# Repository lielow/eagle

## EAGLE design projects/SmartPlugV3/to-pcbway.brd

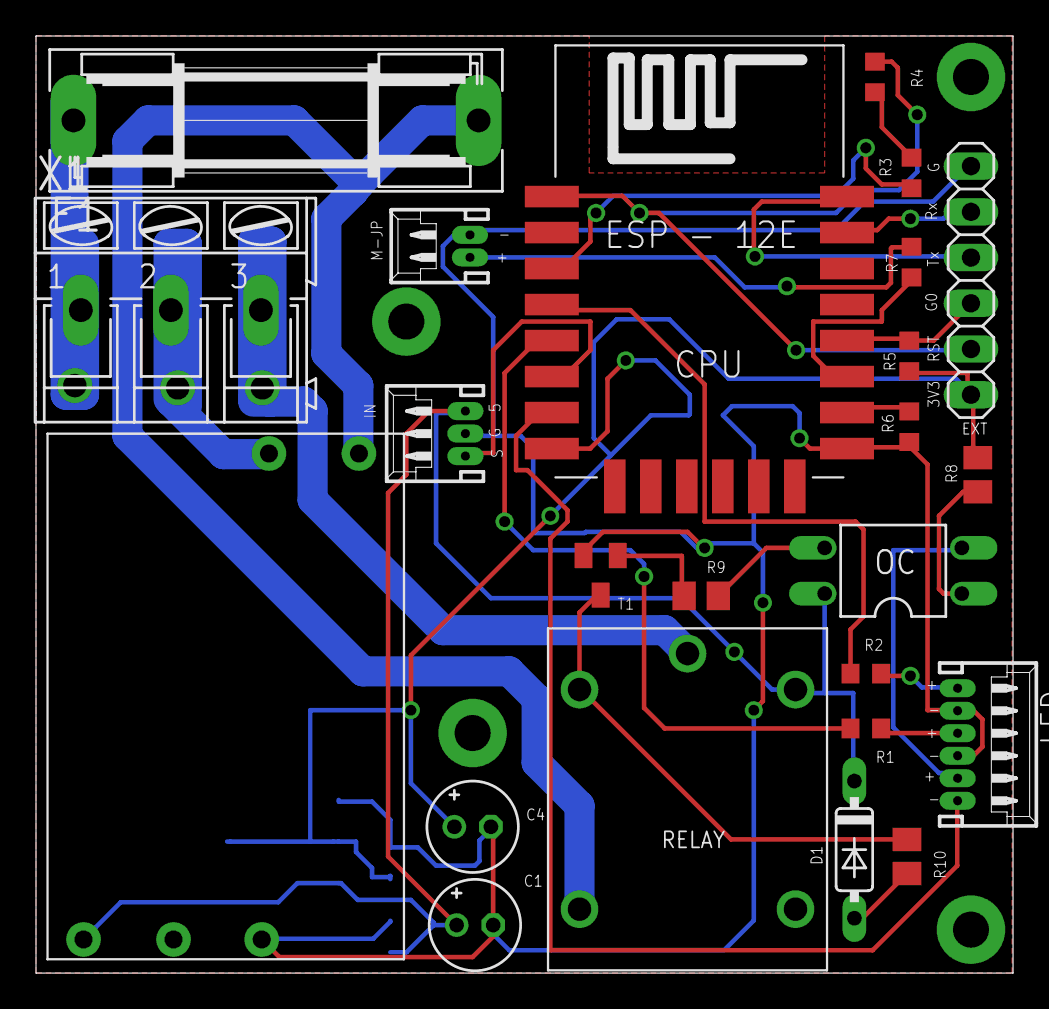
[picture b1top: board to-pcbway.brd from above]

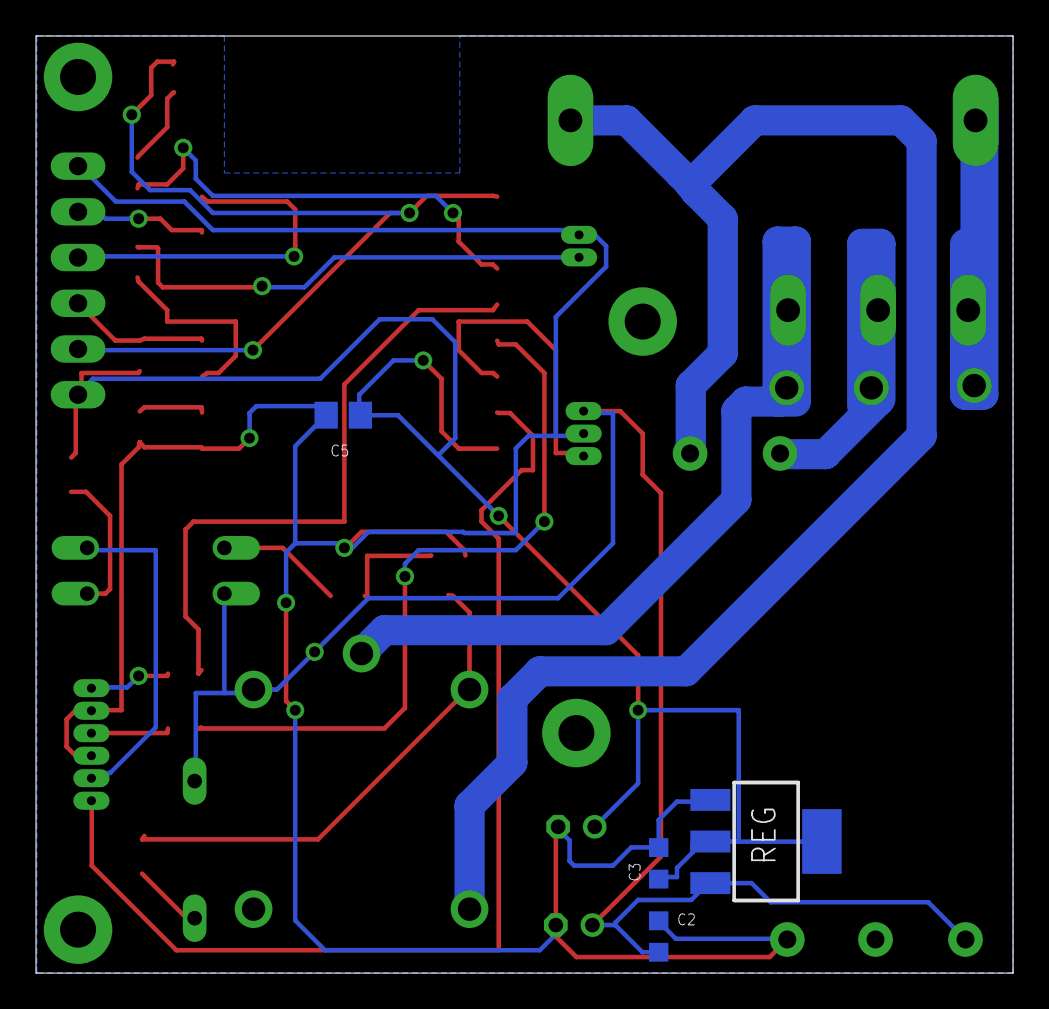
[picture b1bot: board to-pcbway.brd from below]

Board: 2 copper layers, 54.3 x 52.1 mm, 28 parts (4 on the bottom side), 27 nets.

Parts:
C1, C4: E2-5
C2, C3: C0603K
C5: C0805
CPU: ESP12E-SMD
D1: DO35-7
EXT: 1X06
F1: SH22,5
IN: 53048-03
LED: 53048-06
M-JP: 53048-02
OC: DIL04
R1, R2, R3, R4, R5, R6, R7: R0603
R8, R9, R10: M0805
REG: SOT-223
RELAY: RELAY-SONGLE
T1: SOT23-BEC
U$4: POWERSUPPLY-5V-700MA
X1: AK300/3

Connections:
3V3: C3.1, C4.+, C5.1, CPU.VCC, EXT.1, R3.2, R4.2, R5.2, R8.1, REG.2, REG.4
+5V: C1.+, C2.1, D1.C, IN.1, OC.4, REG.3, RELAY.V+, U$4.5V
COM: RELAY.COM, X1.3
EN: CPU.CH_PD, R3.1
G-00: CPU.GPIO0, EXT.3, R5.1
G-12: CPU.GPIO12, IN.3
G-13: CPU.GPIO13, LED.1
G-15: CPU.GPIO15, R6.2
GND: C1.-, C2.2, C3.2, C4.-, C5.2, CPU.GND, EXT.6, IN.2, LED.3, LED.5, M-JP.1, R6.1, REG.1, T1.E, U$4.GND
LED-ESP+: LED.6, R2.1
LED-RELAY+: LED.2, OC.2
LED-STATUS+: LED.4, R1.1
LINE: F1.1, X1.1
M-SW+: M-JP.2, R7.1
N: U$4.AC2, X1.2
unnamed: OC.3, R9.1
unnamed: R9.2, T1.B
unnamed: CPU.GPIO16, R2.2
unnamed: CPU.GPIO2, R7.2
unnamed: CPU.GPIO14, R1.2
unnamed: OC.1, R8.2
unnamed: D1.A, R10.2
unnamed: R10.1, RELAY.V-, T1.C
RELAY-NO: F1.2, RELAY.NO, U$4.AC1
RST: CPU.RESET, EXT.2, R4.1
RX: CPU.RXD0, EXT.5
TX: CPU.TXD0, EXT.4

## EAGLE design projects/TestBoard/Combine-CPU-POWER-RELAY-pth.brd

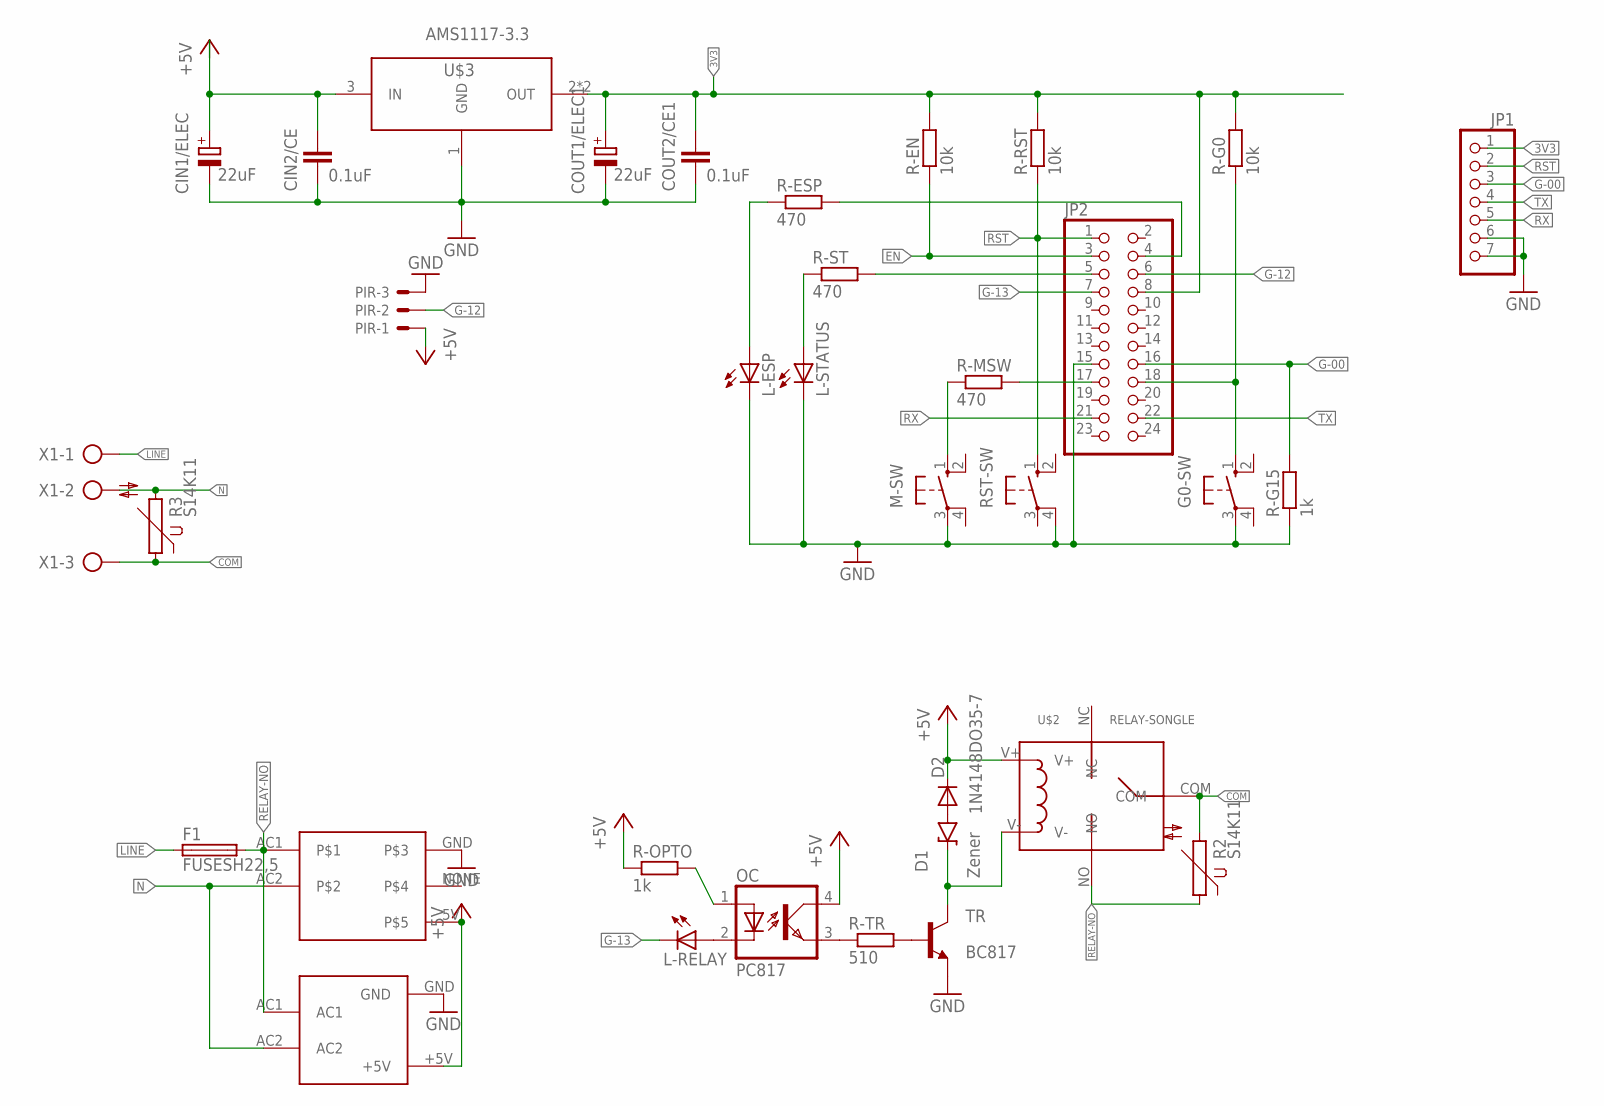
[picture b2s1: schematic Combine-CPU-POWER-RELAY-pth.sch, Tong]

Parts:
CIN1/ELEC: 22uF; E2,5-5
CIN2/CE: 0.1uF; C050-024X044
COUT1/ELEC1: 22uF; E2,5-5
COUT2/CE1: 0.1uF; C050-024X044
D1: Zener; DIODE-ZENER
D2: 1N4148DO35-7; DO35-7
F1: FUSESH22,5; SH22,5
G0-SW: 10-XX; B3F-10XX
JP1: PINHD-1X7; 1X07
JP2: PINHD-2X12; 2X12
L-ESP: LED3MM
L-RELAY: LED3MM
L-STATUS: LED3MM
M-SW: 10-XX; B3F-10XX
OC: PC817; DIL04
PIR: 53048-03
R2, R3: S14K11
R-EN: 10k; 0207/2V
R-ESP: 470; 0207/2V
R-G0: 10k; 0207/2V
R-G15: 1k; 0207/2V
R-MSW: 470; 0207/2V
R-OPTO: 1k; 0207/2V
R-RST: 10k; 0207/2V
R-ST: 470; 0207/2V
R-TR: 510; 0207/2V
RST-SW: 10-XX; B3F-10XX
TR: BC817; SOT23-BEC
U$1: HLK-PM01
U$2: RELAY-SONGLE
U$3: AMS1117-3.3; SOT-223
U$4: POWERSUPPLY-5V-700MA
X1: AK300/3

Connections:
3V3: COUT1/ELEC1.+, COUT2/CE1.1, JP1.1, JP2.8, R-EN.2, R-G0.2, R-RST.2, U$3.2 (OUT), U$3.4 (OUT)
+5V: CIN1/ELEC.+, CIN2/CE.1, D2.C, OC.4 (COL), PIR.1, R-OPTO.1, U$1.+5V, U$2.V+, U$3.3 (IN), U$4.5V
COM: R2.2, R3.1, U$2.COM, X1.3
EN: JP2.3, R-EN.1
G-00: JP1.3, JP2.16, R-G15.2
G-12: JP2.6, PIR.2
G-13: JP2.7, L-RELAY.K (C)
GND: CIN1/ELEC.-, CIN2/CE.2, COUT1/ELEC1.-, COUT2/CE1.2, G0-SW.3, JP1.6, JP1.7, JP2.15, L-ESP.K (C), L-STATUS.K (C), M-SW.3, PIR.3, R-G15.1, RST-SW.4 (P1), TR.E, U$1.GND, U$3.1 (GND), U$4.GND
LINE: F1.1, X1.1
N: R3.2, U$1.AC2, U$4.AC2, X1.2
unnamed: OC.3 (EMIT), R-TR.1
unnamed: R-TR.2, TR.B
unnamed: D1.P$2 (A), D2.A
unnamed: JP2.17, R-MSW.2
unnamed: JP2.5, R-ST.2
unnamed: OC.1 (A), R-OPTO.2
unnamed: D1.P$1 (C), TR.C, U$2.V-
unnamed: JP2.4, R-ESP.2
unnamed: L-RELAY.A, OC.2 (C)
unnamed: M-SW.1 (S), R-MSW.1
unnamed: L-STATUS.A, R-ST.1
unnamed: L-ESP.A, R-ESP.1
unnamed: G0-SW.1 (S), JP2.18, R-G0.1
RELAY-NO: F1.2, R2.1, U$1.AC1, U$2.NO, U$4.AC1
RST: JP1.2, JP2.1, R-RST.1, RST-SW.1 (S)
RX: JP1.5, JP2.21
TX: JP1.4, JP2.22

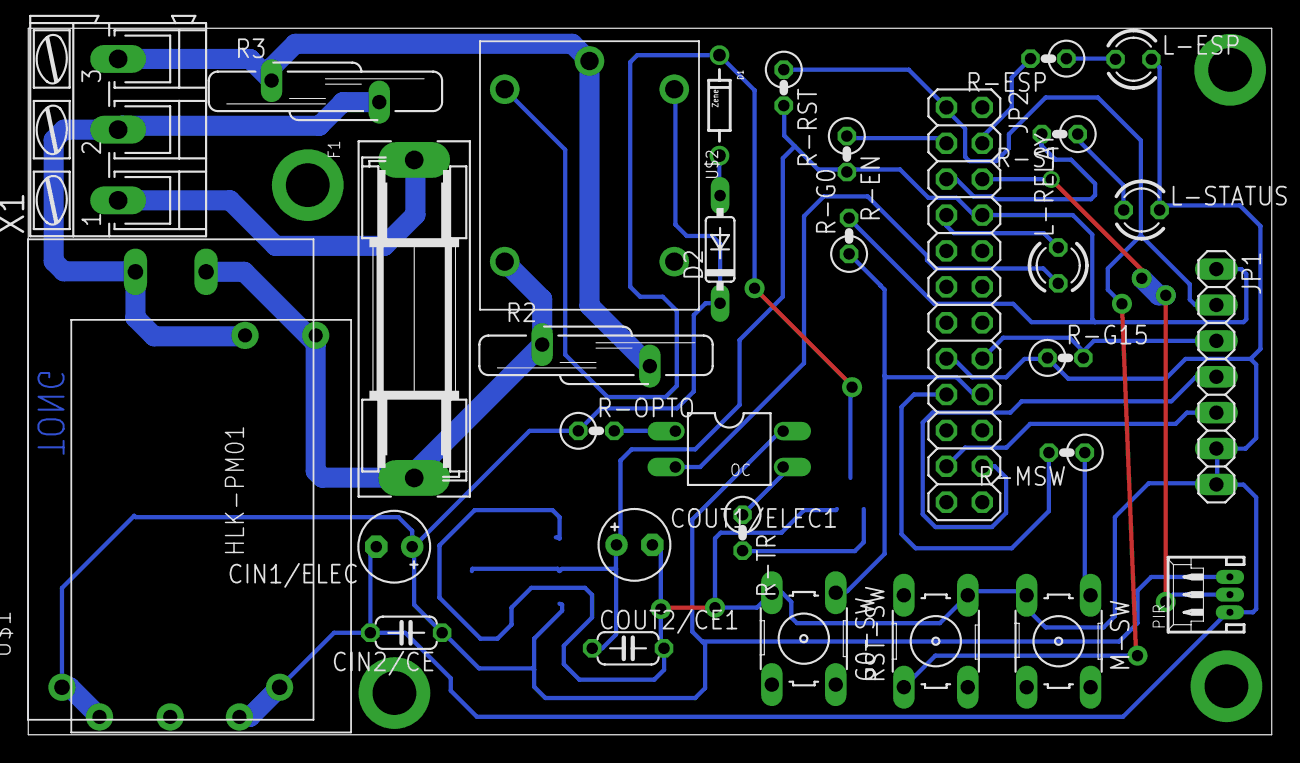
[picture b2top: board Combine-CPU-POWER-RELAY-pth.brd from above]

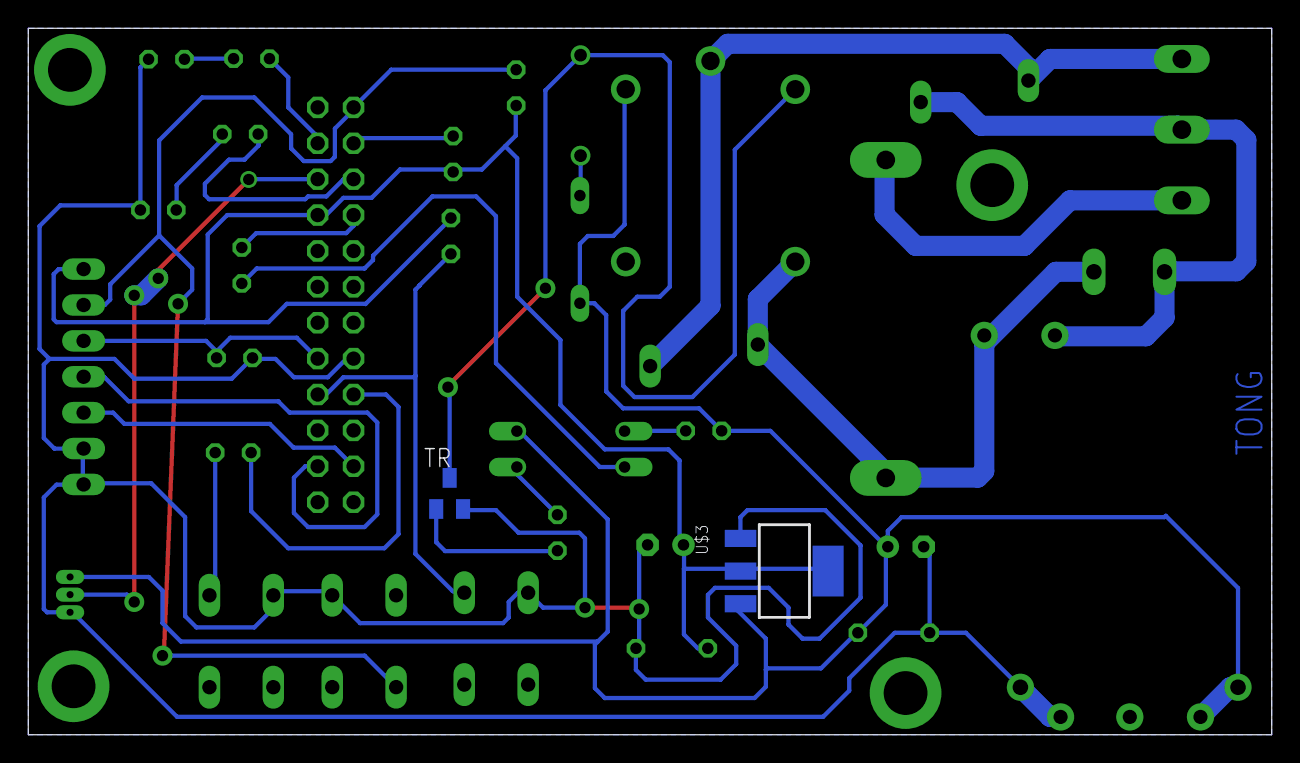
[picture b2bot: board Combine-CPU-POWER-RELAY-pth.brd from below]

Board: 2 copper layers, 88.0 x 50.0 mm, 34 parts (2 on the bottom side), 27 nets.

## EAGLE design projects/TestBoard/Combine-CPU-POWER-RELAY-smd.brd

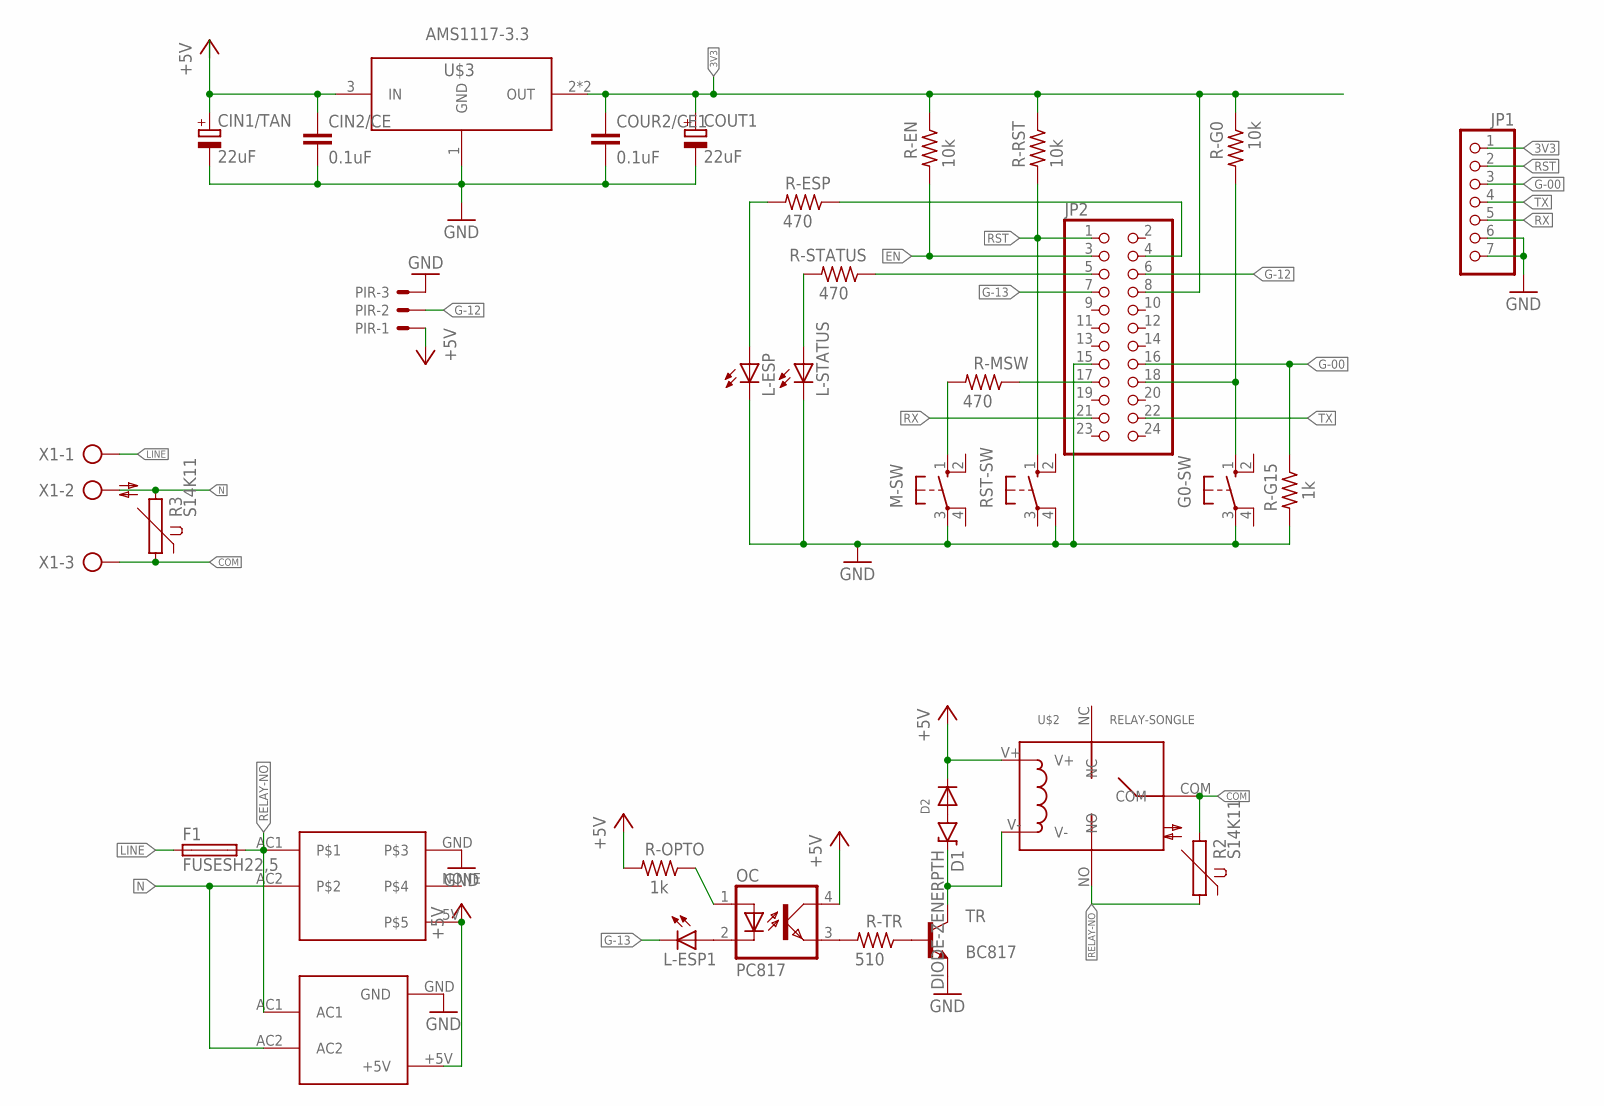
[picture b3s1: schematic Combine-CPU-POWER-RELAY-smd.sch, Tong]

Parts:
CIN1/TAN: 22uF; B/3528-21R
CIN2/CE: 0.1uF; C0805
COUR2/CE1: 0.1uF; C0805
COUT1: 22uF; B/3528-21R
D1: DIODE-ZENERPTH; DIODE-ZENER
D2: DIODESMA; SMADIODE
F1: FUSESH22,5; SH22,5
G0-SW: 10-XX; B3F-10XX
JP1: PINHD-1X7; 1X07
JP2: PINHD-2X12; 2X12
L-ESP, L-ESP1: LED3MM
L-STATUS: LED3MM
M-SW: 10-XX; B3F-10XX
OC: PC817; DIL04
PIR: 53048-03
R2, R3: S14K11
R-EN: 10k; M0805
R-ESP: 470; M0805
R-G0: 10k; M0805
R-G15: 1k; M0805
R-MSW: 470; M0805
R-OPTO: 1k; M0805
R-RST: 10k; M0805
R-STATUS: 470; M0805
R-TR: 510; M0805
RST-SW: 10-XX; B3F-10XX
TR: BC817; SOT23-BEC
U$1: HLK-PM01
U$2: RELAY-SONGLE
U$3: AMS1117-3.3; SOT-223
U$4: POWERSUPPLY-5V-700MA
X1: AK300/3

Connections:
3V3: COUR2/CE1.1, COUT1.+, JP1.1, JP2.8, R-EN.1, R-G0.1, R-RST.1, U$3.2 (OUT), U$3.4 (OUT)
+5V: CIN1/TAN.+, CIN2/CE.1, D2.C, OC.4 (COL), PIR.1, R-OPTO.2, U$1.+5V, U$2.V+, U$3.3 (IN), U$4.5V
COM: R2.2, R3.1, U$2.COM, X1.3
EN: JP2.3, R-EN.2
G-00: JP1.3, JP2.16, R-G15.1
G-12: JP2.6, PIR.2
G-13: JP2.7, L-ESP1.K (C)
GND: CIN1/TAN.-, CIN2/CE.2, COUR2/CE1.2, COUT1.-, G0-SW.3, JP1.6, JP1.7, JP2.15, L-ESP.K (C), L-STATUS.K (C), M-SW.3, PIR.3, R-G15.2, RST-SW.4 (P1), TR.E, U$1.GND, U$3.1 (GND), U$4.GND
LINE: F1.1, X1.1
N: R3.2, U$1.AC2, U$4.AC2, X1.2
unnamed: OC.3 (EMIT), R-TR.2
unnamed: R-TR.1, TR.B
unnamed: JP2.17, R-MSW.1
unnamed: JP2.5, R-STATUS.1
unnamed: OC.1 (A), R-OPTO.1
unnamed: D1.P$2 (A), D2.A
unnamed: D1.P$1 (C), TR.C, U$2.V-
unnamed: JP2.4, R-ESP.1
unnamed: L-ESP1.A, OC.2 (C)
unnamed: M-SW.1 (S), R-MSW.2
unnamed: L-STATUS.A, R-STATUS.2
unnamed: L-ESP.A, R-ESP.2
unnamed: G0-SW.1 (S), JP2.18, R-G0.2
RELAY-NO: F1.2, R2.1, U$1.AC1, U$2.NO, U$4.AC1
RST: JP1.2, JP2.1, R-RST.2, RST-SW.1 (S)
RX: JP1.5, JP2.21
TX: JP1.4, JP2.22

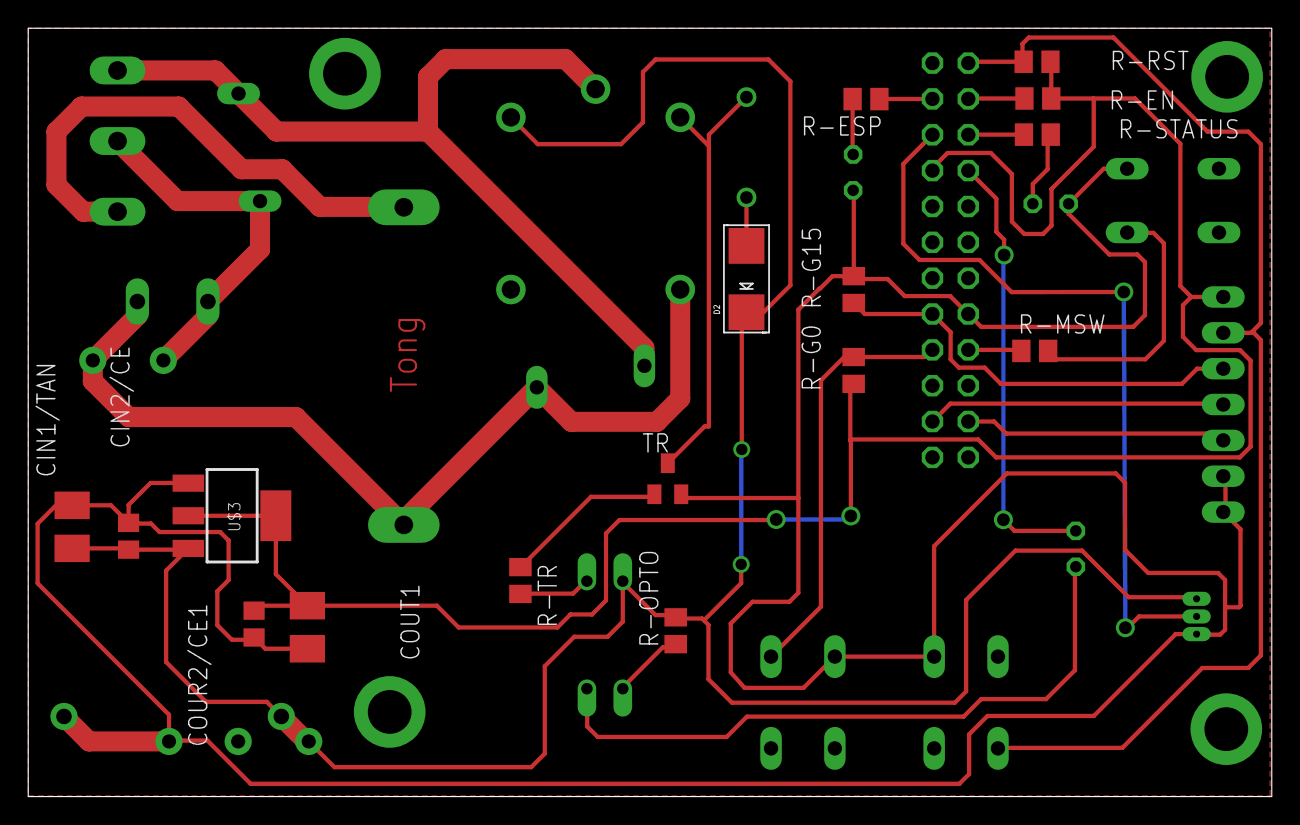
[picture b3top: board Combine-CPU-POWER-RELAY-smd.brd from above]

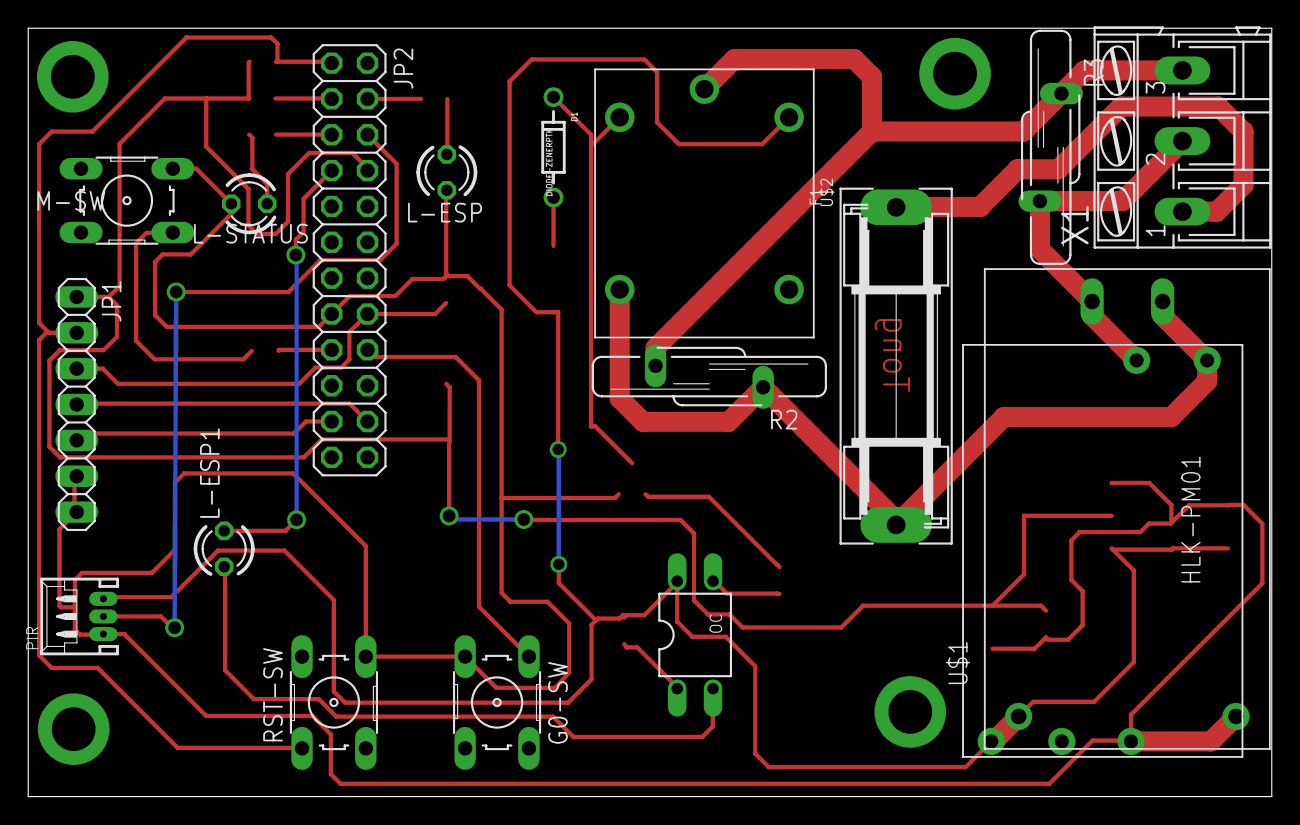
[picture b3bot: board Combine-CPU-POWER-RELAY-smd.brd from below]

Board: 2 copper layers, 88.1 x 54.4 mm, 34 parts (18 on the bottom side), 27 nets.

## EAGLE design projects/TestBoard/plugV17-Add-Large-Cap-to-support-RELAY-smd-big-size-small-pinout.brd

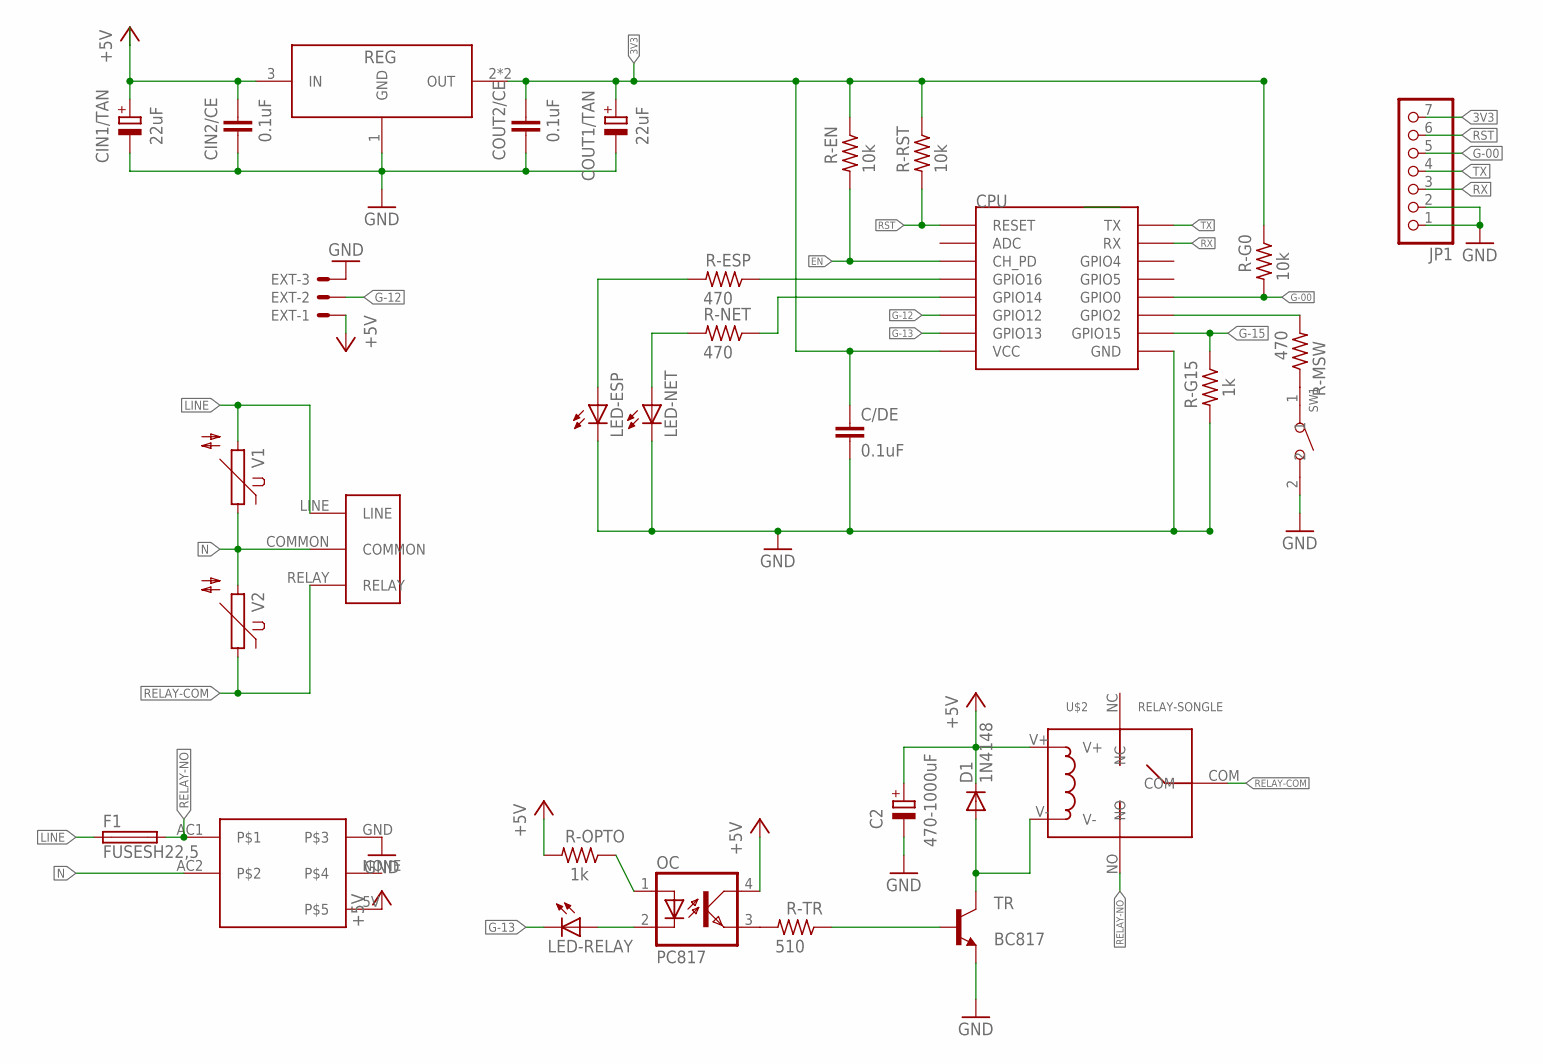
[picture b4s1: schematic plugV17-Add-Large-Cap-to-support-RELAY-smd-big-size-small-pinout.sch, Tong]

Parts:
C2: 470-1000uF; E3,5-8
C/DE: 0.1uF; C0805
CIN1/TAN: 22uF; B/3528-21R
CIN2/CE: 0.1uF; C0805K
COUT1/TAN: 22uF; B/3528-21R
COUT2/CE: 0.1uF; C0805K
CPU: ESP12SMD; ESP12-SMD
D1: 1N4148; DO35-7
EXT: 53048-03
F1: FUSESH22,5; SH22,5
JP1: PINHD-1X7; 1X07
LED-ESP: LEDCHIPLED_0805; CHIPLED_0805
LED-NET: LEDCHIPLED_0805; CHIPLED_0805
LED-RELAY: LEDCHIPLED_0805; CHIPLED_0805
OC: PC817; DIL04
R-EN: 10k; M0805
R-ESP: 470; M0805
R-G0: 10k; M0805
R-G15: 1k; M0805
R-MSW: 470; M0805
R-NET: 470; M0805
R-OPTO: 1k; M0805
R-RST: 10k; M0805
R-TR: 510; M0805
REG: AMS1117-3.3; SOT-223
SW1: DIP-BUTTON(2P-6.0X3.0X4.3MM)-TS-1101F; SW2-5.0-6.0X3.0X4.3MM
TR: BC817; SOT23-BEC
U$1: POWER-RELAY-FOOTPRINT
U$2: RELAY-SONGLE
U$4: POWERSUPPLY-5V-700MA
V1, V2: S14K11

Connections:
3V3: C/DE.1, COUT1/TAN.+, COUT2/CE.1, CPU.VCC, JP1.7, R-EN.1, R-G0.1, R-RST.1, REG.2 (OUT), REG.4 (OUT)
+5V: C2.+, CIN1/TAN.+, CIN2/CE.1, D1.C, EXT.1, OC.4 (COL), R-OPTO.2, REG.3 (IN), U$2.V+, U$4.5V
EN: CPU.CH_PD, R-EN.2
G-00: CPU.GPIO0, JP1.5, R-G0.2
G-12: CPU.GPIO12, EXT.2
G-13: CPU.GPIO13, LED-RELAY.C
G-15: CPU.GPIO15, R-G15.1
GND: C2.-, C/DE.2, CIN1/TAN.-, CIN2/CE.2, COUT1/TAN.-, COUT2/CE.2, CPU.GND, EXT.3, JP1.1, JP1.2, LED-ESP.C, LED-NET.C, R-G15.2, REG.1 (GND), SW1.2, TR.E, U$4.GND
LINE: F1.1, U$1.LINE, V1.2
N: U$1.COMMON, U$4.AC2, V1.1, V2.2
unnamed: OC.3 (EMIT), R-TR.2
unnamed: R-TR.1, TR.B
unnamed: R-MSW.1, SW1.1
unnamed: LED-ESP.A, R-ESP.2
unnamed: CPU.GPIO2, R-MSW.2
unnamed: CPU.GPIO14, R-NET.1
unnamed: OC.1 (A), R-OPTO.1
unnamed: LED-NET.A, R-NET.2
unnamed: D1.A, TR.C, U$2.V-
unnamed: CPU.GPIO16, R-ESP.1
unnamed: LED-RELAY.A, OC.2 (C)
RELAY-COM: U$1.RELAY, U$2.COM, V2.1
RELAY-NO: F1.2, U$2.NO, U$4.AC1
RST: CPU.RESET, JP1.6, R-RST.2
RX: CPU.RXD0 (RX), JP1.3
TX: CPU.TXD0 (TX), JP1.4

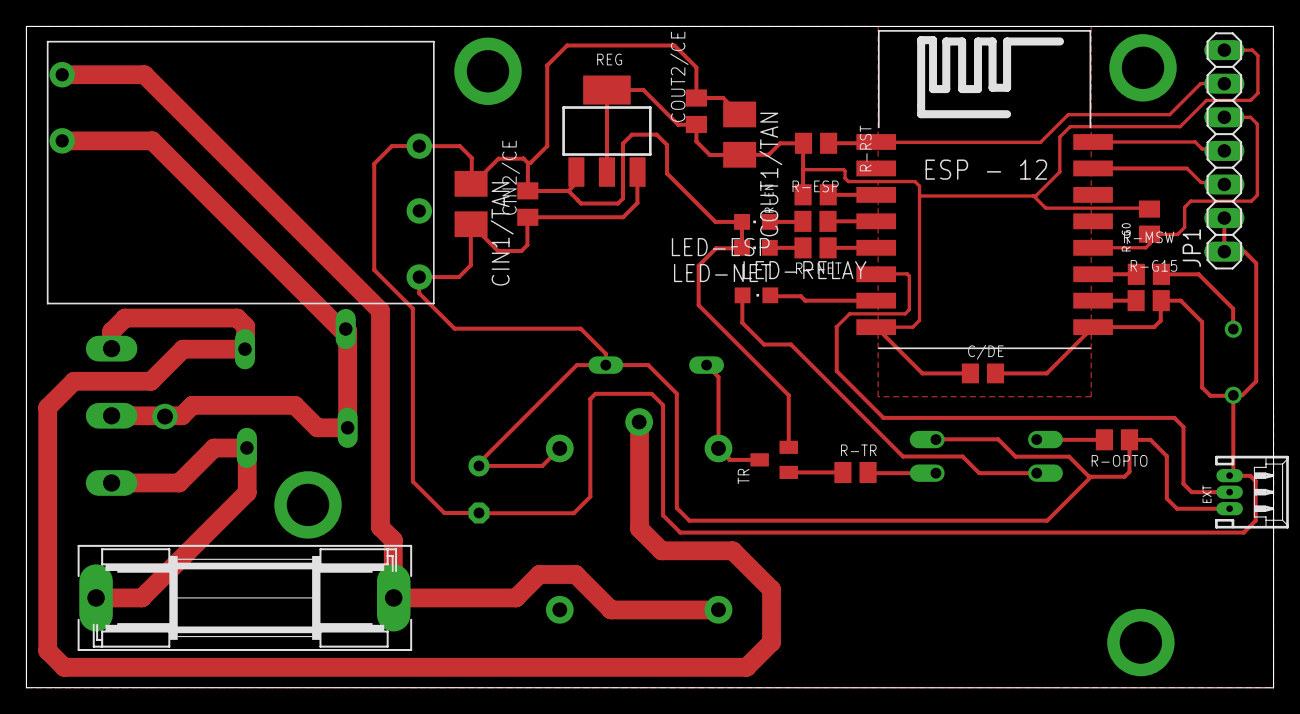
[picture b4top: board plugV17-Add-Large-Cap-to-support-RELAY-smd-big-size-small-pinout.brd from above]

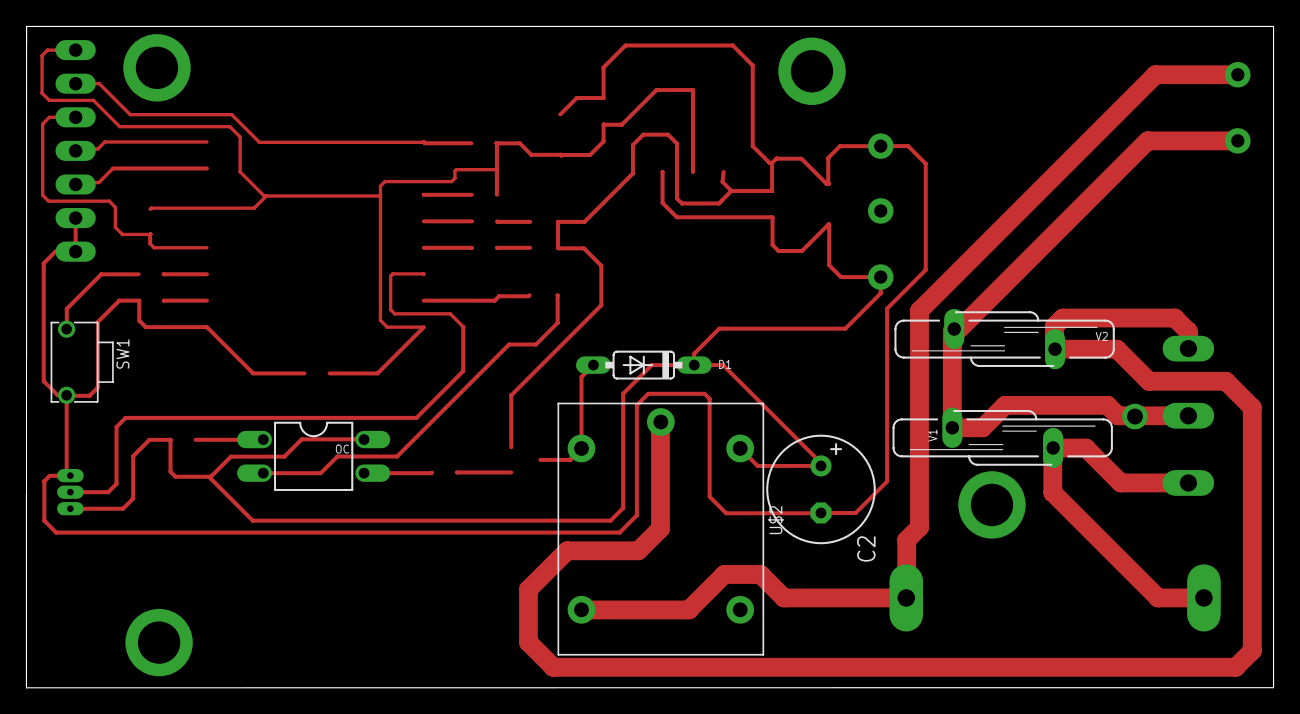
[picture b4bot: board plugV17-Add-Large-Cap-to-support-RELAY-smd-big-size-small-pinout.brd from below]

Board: 2 copper layers, 94.3 x 50.0 mm, 32 parts (8 on the bottom side), 26 nets.

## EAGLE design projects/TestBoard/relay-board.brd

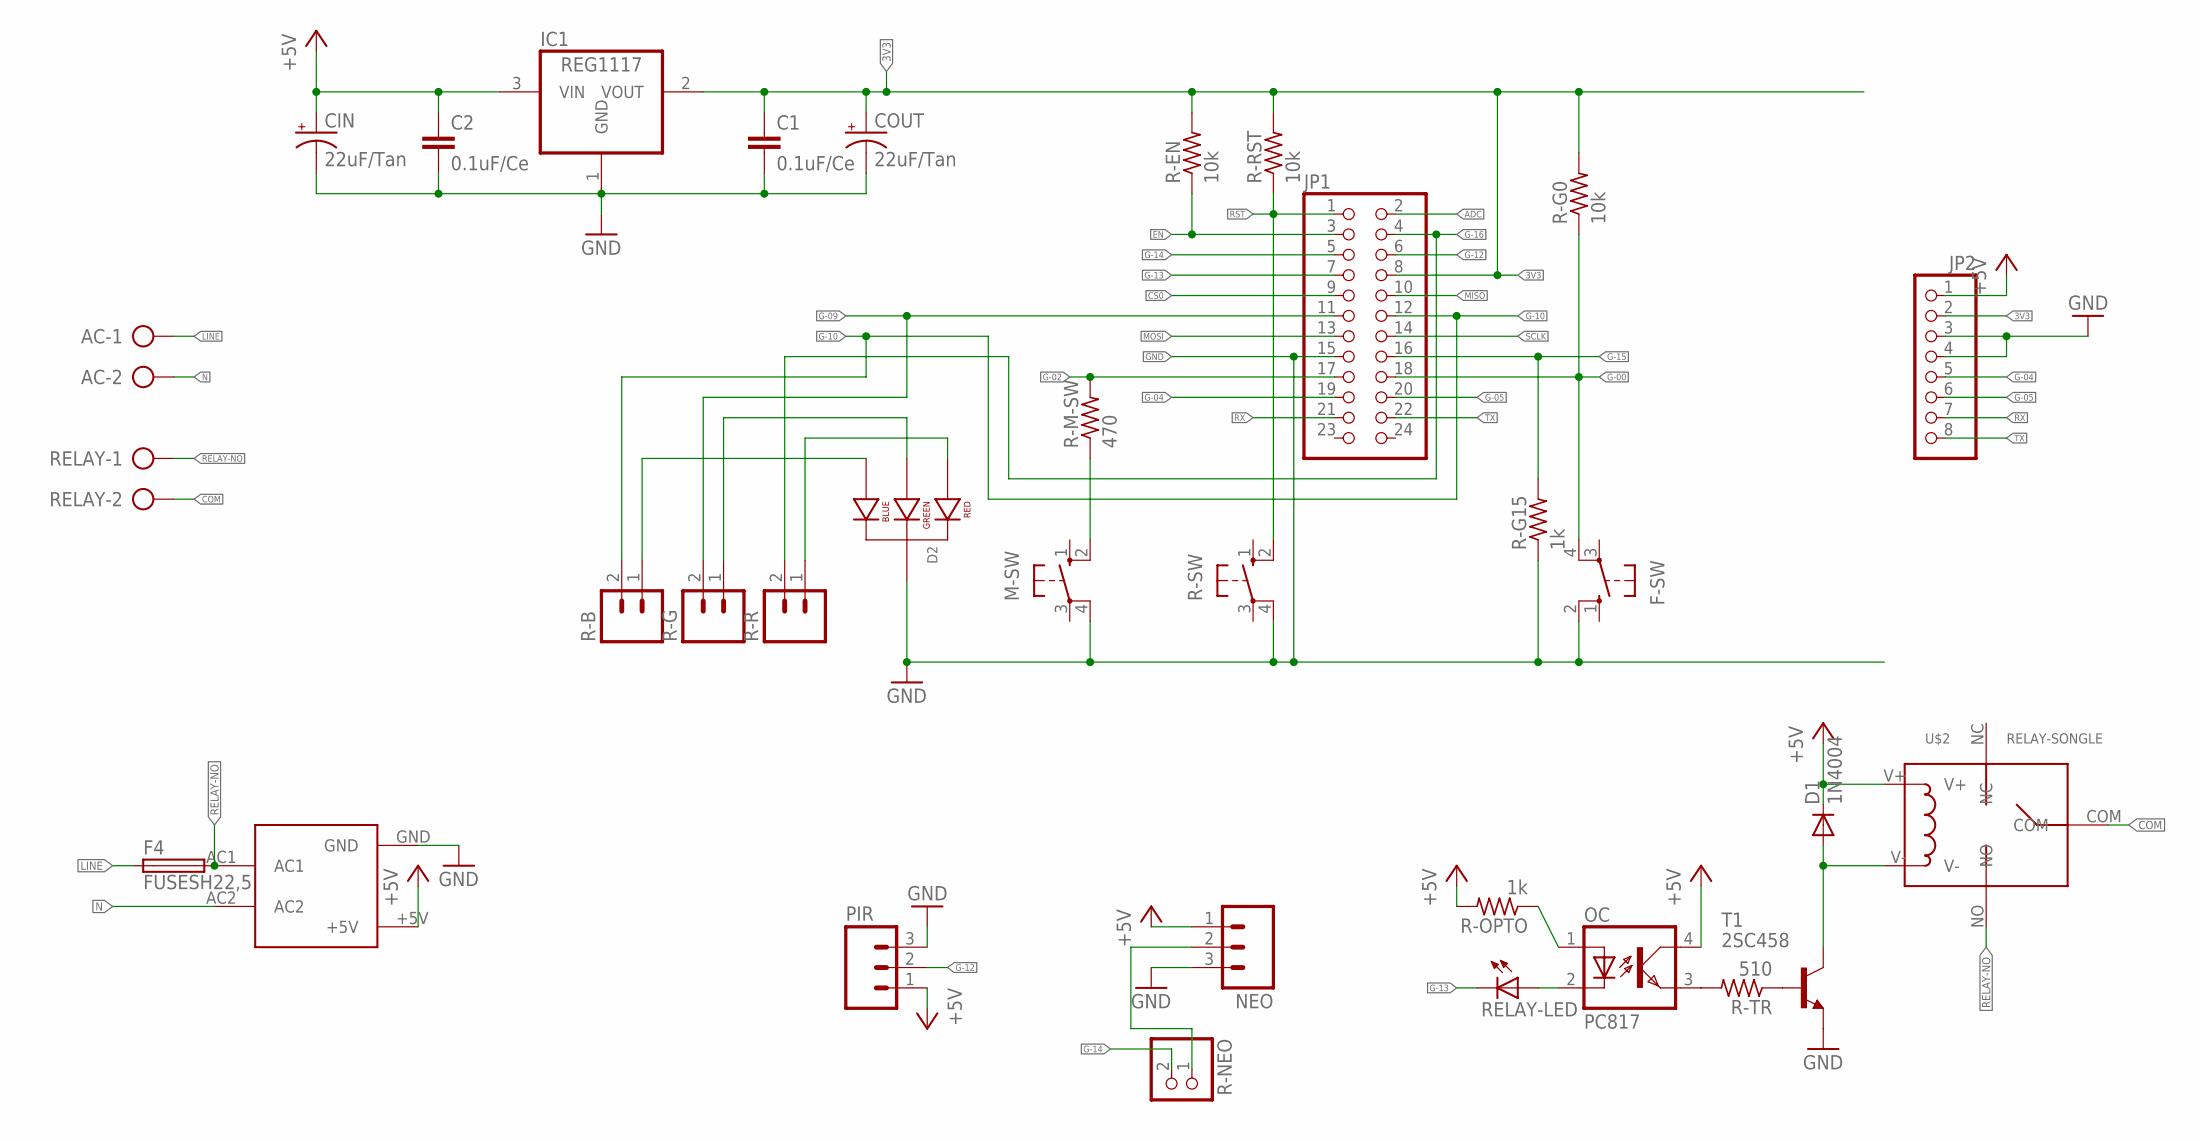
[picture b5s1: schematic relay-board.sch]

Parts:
AC: AK300/2
C1, C2: 0.1uF/Ce; C025-024X044
CIN: 22uF/Tan; E2,5-5
COUT: 22uF/Tan; E2,5-5
D1: 1N4004; DO41-10
D2: LED-RGB-CC-THRU; LED-RGB-THRU
F4: FUSESH22,5; SH22,5
F-SW: 10-XX; B3F-10XX
IC1: REG1117; SOT223
JP1: PINHD-2X12; 2X12
JP2: PINHD-1X8; 1X08
M-SW: 10-XX; B3F-10XX
NEO: M03POLAR; MOLEX-1X3
OC: PC817; DIL04
PIR: M03POLAR; MOLEX-1X3
R-B: M02PTH; 1X02
R-EN: 10k; 0207/7
R-G: M02PTH; 1X02
R-G0: 10k; 0207/7
R-G15: 1k; 0207/7
R-M-SW: 470; 0207/7
R-NEO: PINHD-1X2; 1X02
R-OPTO: 1k; 0207/7
R-R: M02PTH; 1X02
R-RST: 10k; 0207/7
R-SW: 10-XX; B3F-10XX
R-TR: 510; 0207/7
RELAY: AK300/2
RELAY-LED: LED3MM
T1: 2SC458; TO92-ECB
U$1: HLK-PM01
U$2: RELAY-SONGLE

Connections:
3V3: C1.1, COUT.+, IC1.2 (VOUT), JP1.8, JP2.2, R-EN.2, R-G0.2, R-RST.2
+5V: C2.1, CIN.+, D1.C, IC1.3 (VIN), JP2.1, NEO.1, OC.4 (COL), PIR.1, R-OPTO.2, U$1.+5V, U$2.V+
ADC: JP1.2
COM: RELAY.2, U$2.COM
CS0: JP1.9
EN: JP1.3, R-EN.1
G-00: F-SW.4 (P1), JP1.18, R-G0.1
G-02: JP1.17, R-M-SW.2
G-04: JP1.19, JP2.5
G-05: JP1.20, JP2.6
G-09: JP1.11, R-G.2
G-10: JP1.12, R-B.2
G-12: JP1.6, PIR.2
G-13: JP1.7, RELAY-LED.K (C)
G-14: JP1.5, R-NEO.2
G-15: JP1.16, R-G15.2
G-16: JP1.4, R-R.2
GND: C1.2, C2.2, CIN.-, COUT.-, D2.P$2 (CATHODE), F-SW.2 (S1), IC1.1 (GND), JP1.15, JP2.3, JP2.4, M-SW.4 (P1), NEO.3, PIR.3, R-G15.1, R-SW.4 (P1), T1.E, U$1.GND
LINE: AC.1, F4.1
MISO: JP1.10
MOSI: JP1.13
N: AC.2, U$1.AC2
unnamed: OC.3 (EMIT), R-TR.2
unnamed: R-TR.1, T1.B
unnamed: D2.P$1 (RED_CATHODE), R-R.1
unnamed: D2.P$3 (GREEN_CATHODE), R-G.1
unnamed: D2.P$4 (BLUE_CATHODE), R-B.1
unnamed: OC.2 (C), RELAY-LED.A
unnamed: NEO.2, R-NEO.1
unnamed: M-SW.2 (S1), R-M-SW.1
unnamed: OC.1 (A), R-OPTO.1
unnamed: D1.A, T1.C, U$2.V-
RELAY-NO: F4.2, RELAY.1, U$1.AC1, U$2.NO
RST: JP1.1, R-RST.1, R-SW.2 (S1)
RX: JP1.21, JP2.7
SCLK: JP1.14
TX: JP1.22, JP2.8

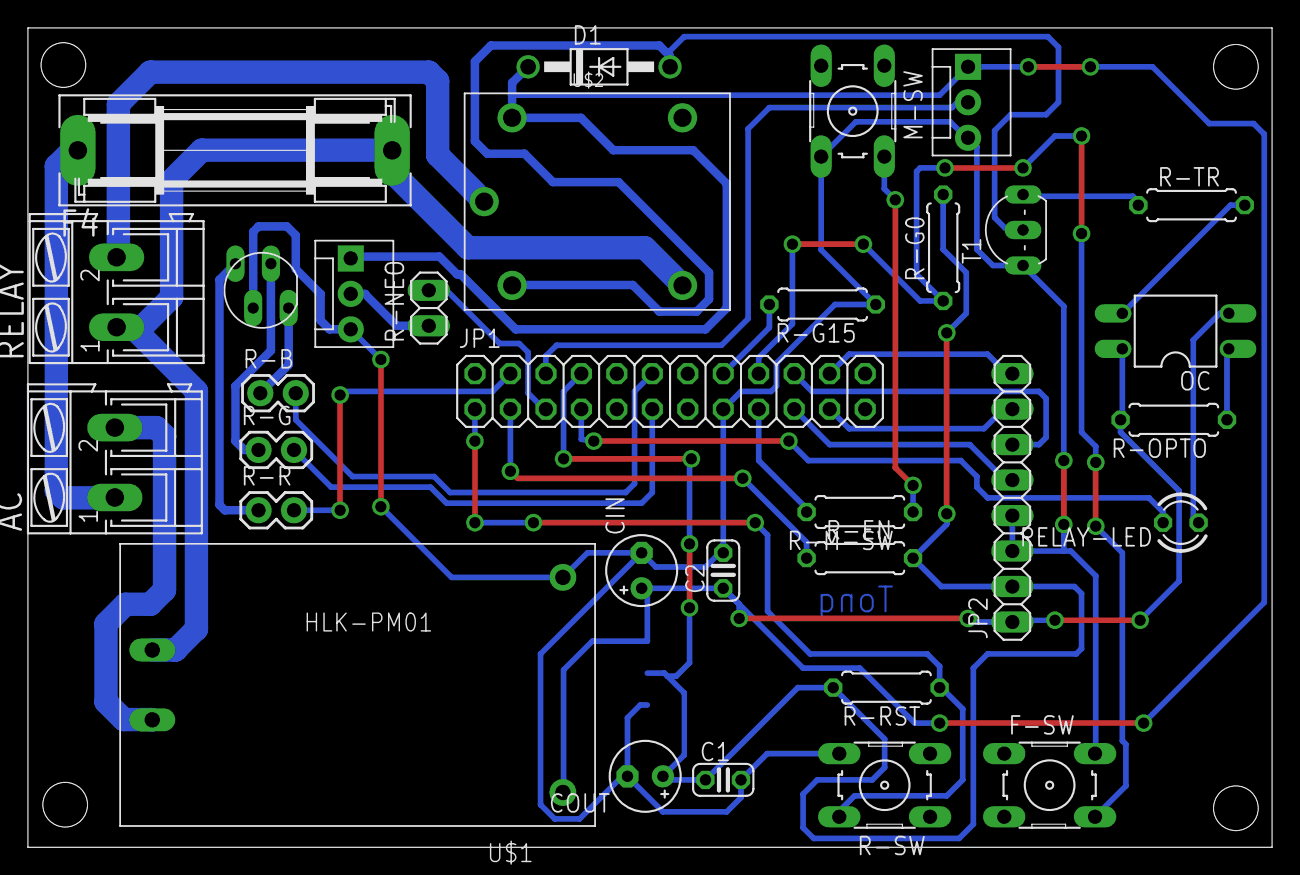
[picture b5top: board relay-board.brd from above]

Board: 2 copper layers, 89.1 x 58.7 mm, 33 parts (1 on the bottom side), 32 nets.

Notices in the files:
parts and their libraries:
SparkFun-DiscreteSemi: Licensing: Creative Commons ShareAlike 4.0 International - https://creativecommons.org/licenses/by-sa/4.0
DIY-Modules: Released under the Creative Commons Attribution 4.0 International License: http://creativecommons.org/licenses/by/4.0
